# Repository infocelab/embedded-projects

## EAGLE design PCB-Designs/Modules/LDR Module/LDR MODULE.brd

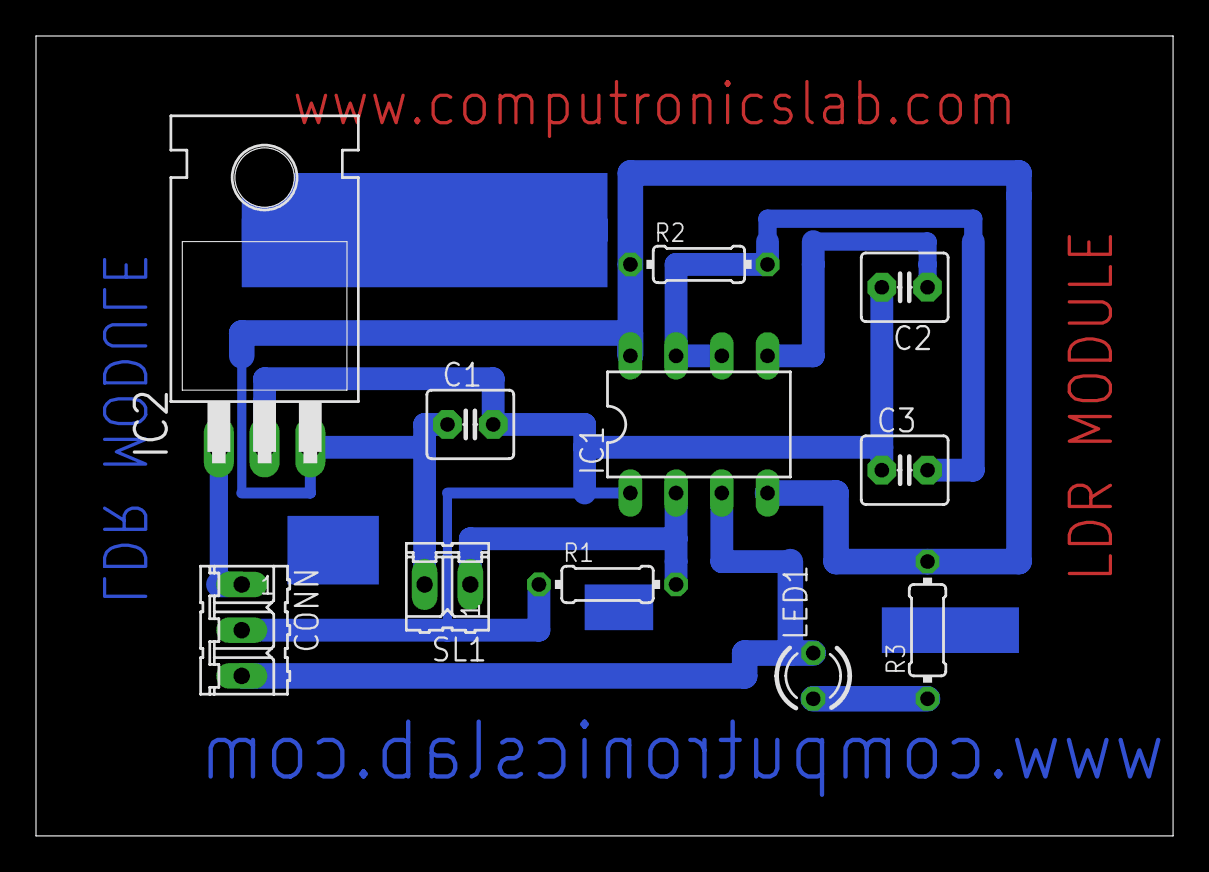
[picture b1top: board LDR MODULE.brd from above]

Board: 2 copper layers, 63.2 x 44.4 mm, 11 parts (0 on the bottom side), 8 nets.

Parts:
C1: .001uf; C2.5-4
C2: 0.01uf; C2.5-4
C3: 0.001uf; C2.5-4
CONN: 3 PIN; 03P
IC1: NE555; DIL-08
IC2: 7805T; TO220H
LED1: 3MM; LED3MM
R1: 10K; 0204/7
R2: 100K; 0204/7
R3: 330E; 0204/7
SL1: LDR; 02P

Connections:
unnamed: C1.1, IC1.4, IC1.8, IC2.3, R2.1, R3.2, SL1.2
unnamed: C3.2, IC1.6, IC1.7, R2.2
unnamed: C2.1, IC1.5
unnamed: IC1.2, R1.2, SL1.1
unnamed: C1.2, C2.2, C3.1, CONN.2, IC1.1, IC2.2, R1.1
unnamed: CONN.3, IC1.3, LED1.K
unnamed: LED1.A, R3.1
unnamed: CONN.1, IC2.1

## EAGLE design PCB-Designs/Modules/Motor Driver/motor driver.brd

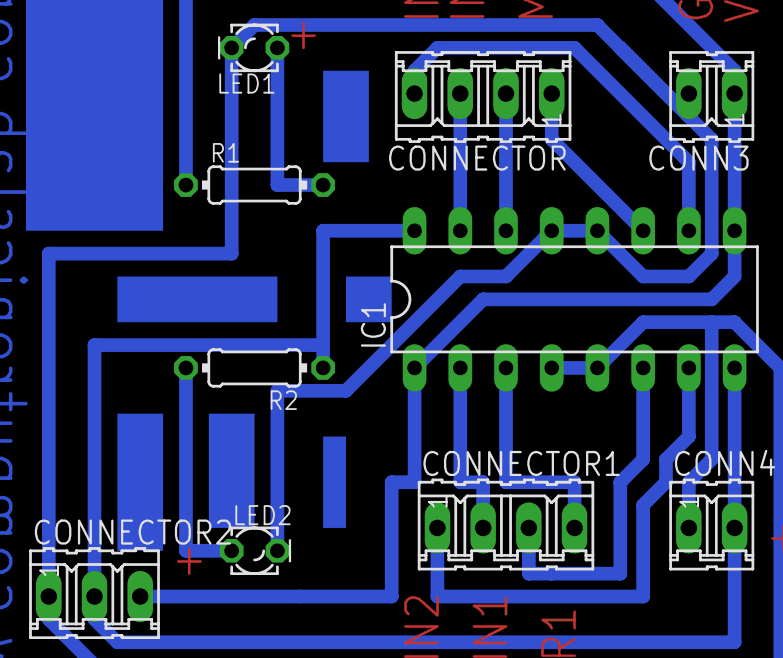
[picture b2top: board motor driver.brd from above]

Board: 2 copper layers, 10 parts (0 on the bottom side), 13 nets.

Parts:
CONN3, CONN4: 2 pin; 02P
CONNECTOR, CONNECTOR1: 4 pin; 04P
CONNECTOR2: 3 pin; 03P
IC1: L293D; DIL16
LED1, LED2: 5mm; LED_LD260
R1, R2: 330E; 0204/7

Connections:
unnamed: LED1.A, R1.2
unnamed: LED2.A, R2.2
unnamed: CONNECTOR1.2, IC1.2
unnamed: CONNECTOR1.4, IC1.3
unnamed: CONNECTOR1.3, IC1.6
unnamed: CONNECTOR1.1, IC1.7
unnamed: CONNECTOR.3, IC1.15
unnamed: CONNECTOR.4, IC1.10
unnamed: CONNECTOR.2, IC1.14
unnamed: CONNECTOR.1, IC1.11
unnamed: CONN3.2, CONN4.1, CONNECTOR2.1, IC1.4, IC1.5, IC1.12, IC1.13, LED1.K, LED2.K
unnamed: CONN3.1, CONNECTOR2.3, IC1.1, IC1.9, R1.1
unnamed: CONN4.2, CONNECTOR2.2, IC1.8, IC1.16, R2.1

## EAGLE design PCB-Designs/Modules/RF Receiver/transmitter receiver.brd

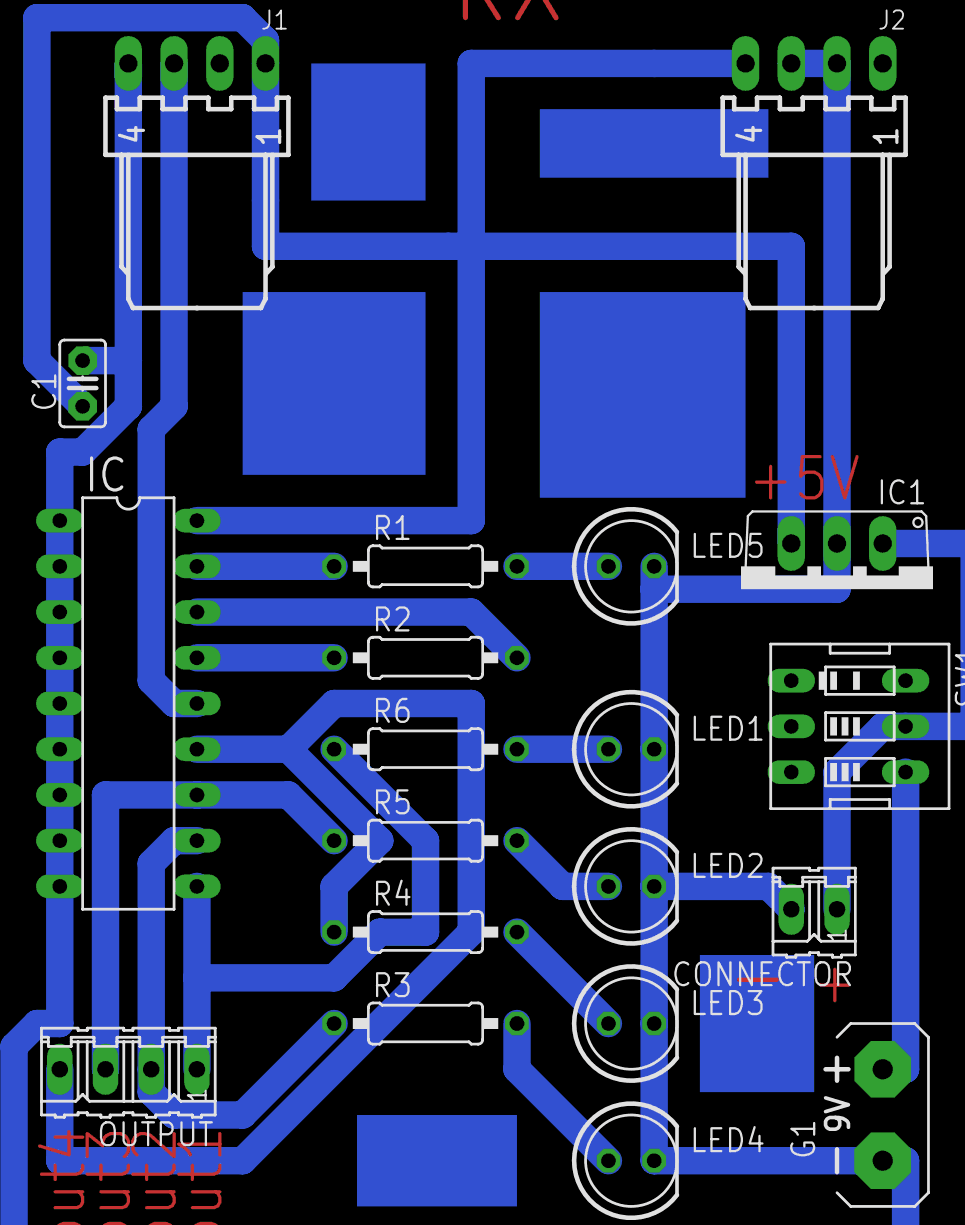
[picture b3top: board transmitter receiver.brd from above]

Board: 2 copper layers, 20 parts (0 on the bottom side), 17 nets.

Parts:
C1: .01uf (103); C2.5-2
CONNECTOR: 2 pin; 02P
G1: AB9V
IC: HT12D; DIL18
IC1: 7805TV; TO220V
J1, J2: female conn; 7395-04
LED1, LED2, LED3, LED4, LED5: 5mm; LED5MM
OUTPUT: 4 pin; 04P
R1, R3, R4, R5, R6: 330E; 0207/10
R2: 47K; 0207/10
SW1: on/off switch; EDG-03

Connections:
FEMALECONN: IC.14, J1.3
unnamed: LED3.A, R4.2
unnamed: LED2.A, R5.2
unnamed: LED4.A, R3.2
unnamed: LED1.A, R6.2
unnamed: IC.15, R2.1
unnamed: IC.17, R1.1
unnamed: LED5.A, R1.2
unnamed: IC.13, OUTPUT.4, R4.1
unnamed: IC.12, OUTPUT.3, R5.1
unnamed: IC.11, OUTPUT.2, R3.1
unnamed: IC.10, OUTPUT.1, R6.1
unnamed: C1.1, IC.18, IC1.3, J1.1, J2.4
unnamed: C1.2, CONNECTOR.2, G1.-, IC.1, IC.2, IC.3, IC.4, IC.5, IC.6, IC.7, IC.8, IC.9, IC1.2, J1.4, J2.2, J2.3, LED1.K, LED2.K, LED3.K, LED4.K, LED5.K
unnamed: G1.+, SW1.4
unnamed: CONNECTOR.1, IC1.1, SW1.5
unnamed: IC.16, R2.2

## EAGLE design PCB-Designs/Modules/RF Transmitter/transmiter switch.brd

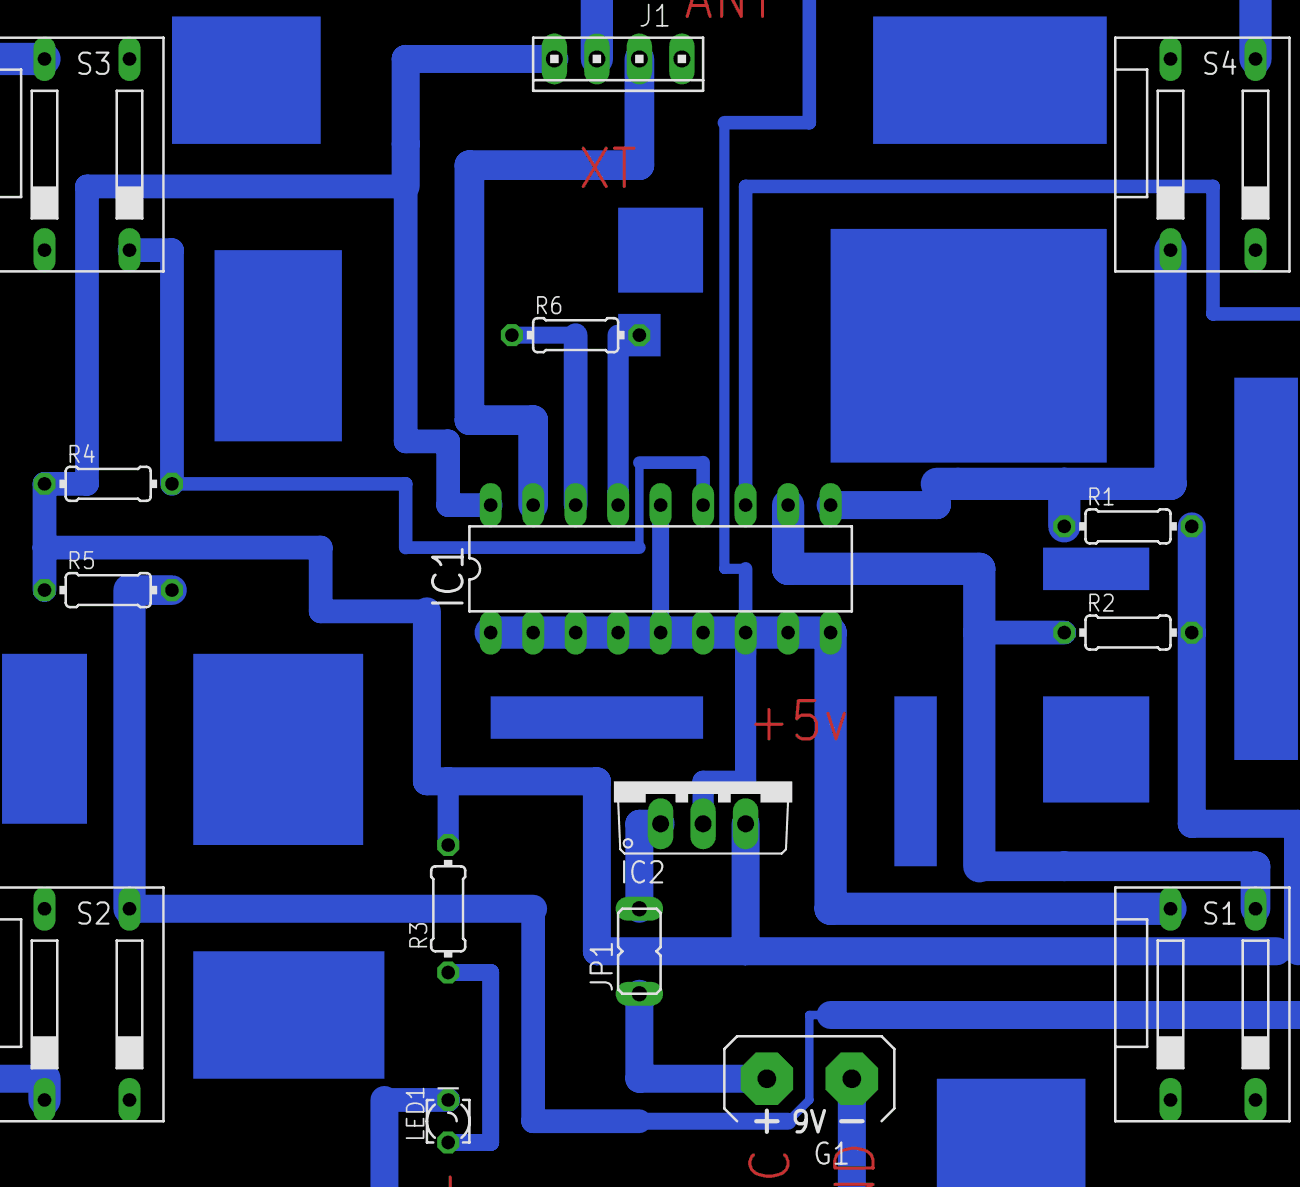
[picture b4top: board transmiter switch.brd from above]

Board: 2 copper layers, 16 parts (0 on the bottom side), 12 nets.

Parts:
G1: AB9V
IC1: HT12E; DIL18
IC2: 7805TV; TO220V
J1: transmitter; 10X04MTA
JP1: jumper; JP1
LED1: 5mm; LED_LD260
R1, R2, R4, R5: 1k; 0204/7
R3: 330E; 0204/7
R6: 1ME; 0204/7
S1: push switch 1; DS-02
S2: push switch2; DS-02
S3: push switch 3; DS-02
S4: push switch 4; DS-02

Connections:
unnamed: LED1.A, R3.1
unnamed: IC1.10, R1.1, S4.1
unnamed: IC1.11, R2.1, S1.3
unnamed: IC1.12, R5.2, S2.3
unnamed: IC1.13, R4.2, S3.2
unnamed: IC1.16, R6.1
unnamed: IC1.15, R6.2
unnamed: IC1.18, IC2.3, J1.1, R1.2, R2.2, R3.2, R4.1, R5.1
unnamed: IC1.17, J1.3
unnamed: G1.-, IC1.1, IC1.2, IC1.3, IC1.4, IC1.5, IC1.6, IC1.7, IC1.8, IC1.9, IC1.14, IC2.2, J1.2, LED1.K, S1.4, S2.1, S3.4, S4.3
unnamed: G1.+, JP1.1
unnamed: IC2.1, JP1.2

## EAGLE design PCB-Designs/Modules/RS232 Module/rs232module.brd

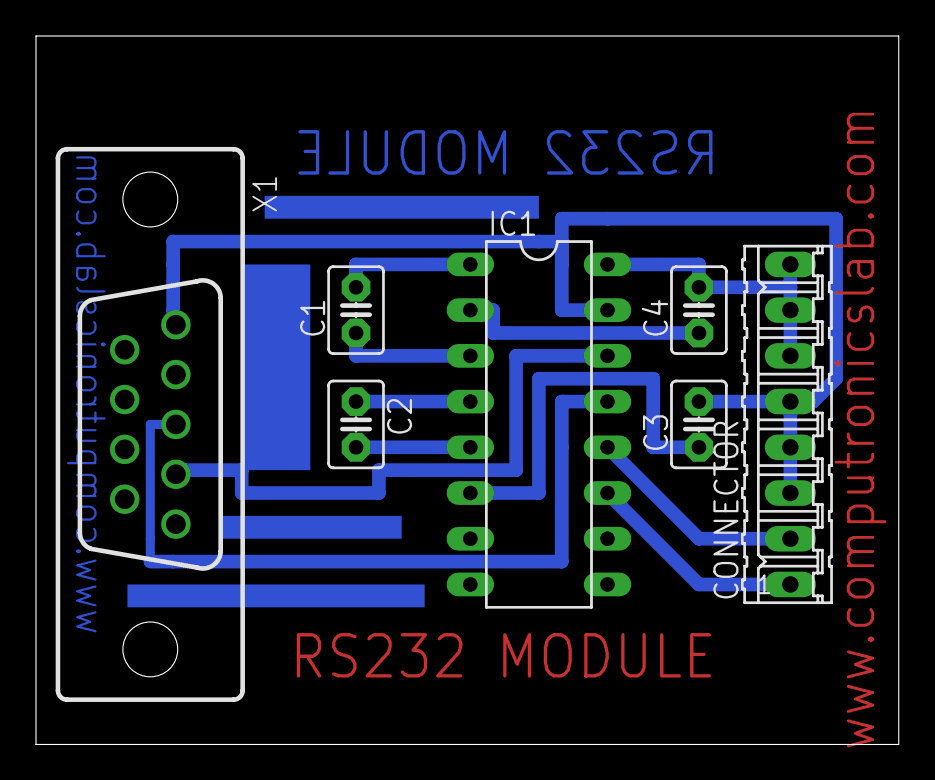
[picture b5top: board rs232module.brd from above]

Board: 2 copper layers, 47.9 x 39.4 mm, 7 parts (0 on the bottom side), 12 nets.

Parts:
C1, C2, C3, C4: 0.1uf; C2.5-3
CONNECTOR: 8 pin; 08P
IC1: MAX232; DIL16
X1: DB 9 FEMALE; H2M09ST

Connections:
unnamed: C1.2, IC1.1
unnamed: C1.1, IC1.3
unnamed: C2.1, IC1.4
unnamed: C2.2, IC1.5
unnamed: C3.1, IC1.6
unnamed: C3.2, CONNECTOR.3, CONNECTOR.4, CONNECTOR.5, IC1.15, X1.1
unnamed: C4.1, IC1.2
unnamed: C4.2, CONNECTOR.6, CONNECTOR.7, CONNECTOR.8, IC1.16
unnamed: IC1.13, X1.3
unnamed: IC1.14, X1.4
unnamed: CONNECTOR.1, IC1.11
unnamed: CONNECTOR.2, IC1.12

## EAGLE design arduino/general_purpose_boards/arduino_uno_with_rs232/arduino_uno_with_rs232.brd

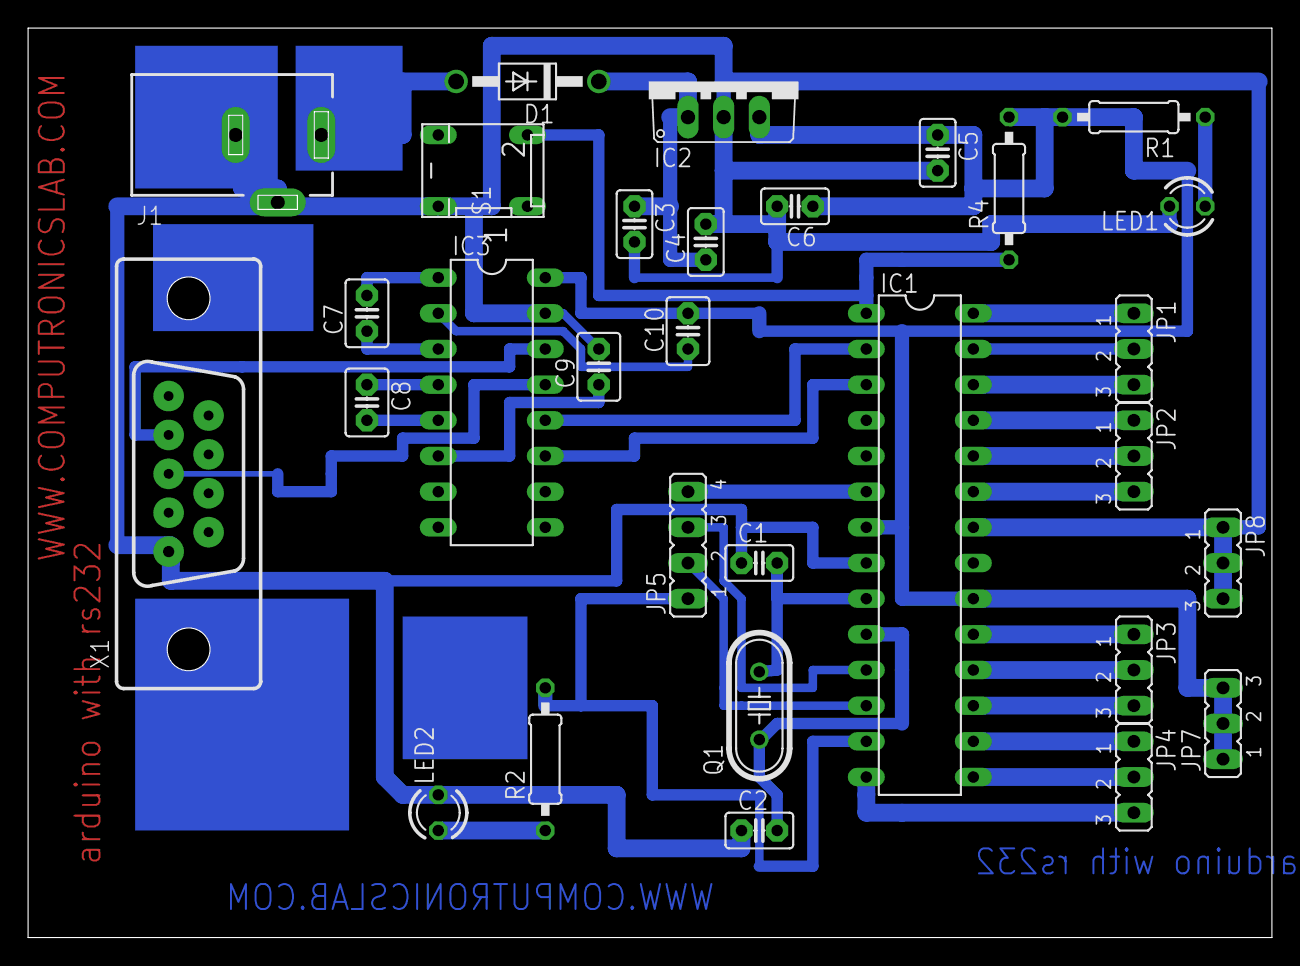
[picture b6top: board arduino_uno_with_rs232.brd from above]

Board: 2 copper layers, 88.6 x 64.8 mm, 30 parts (0 on the bottom side), 35 nets.

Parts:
C1, C2: 22pf; C2.5-2
C3: 100UF; C2.5-2
C4, C5: 0.1uf; C2.5-2
C6: 4.7uf; C2.5-2
C7, C8, C9, C10: 0.1uf; C2.5-3
D1: 1N4007; DO41-10
IC1: ATMEGA328; DIL28-3
IC2: 7805; TO220V
IC3: MAX232; DIL16
J1: DCJ0303
JP1, JP2, JP3, JP4, JP7, JP8: JP2
JP5: JP4
LED1, LED2: LED3MM
Q1: 12MHZ; HC49/S
R1: 220R; 0207/10
R2: 330R; 0207/10
R4: 10K; 0207/10
S1: DP-02
X1: DB 9 FEMALE; H2M09ST

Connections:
unnamed: C1.2, IC1.9, Q1.2
unnamed: C2.2, IC1.10, Q1.1
unnamed: D1.A, J1.1
unnamed: LED1.A, R1.1
unnamed: C3.1, C4.1, D1.C, IC2.1
unnamed: IC1.28, JP1.1
unnamed: IC1.27, JP1.2
unnamed: IC1.26, JP1.3
unnamed: IC1.25, JP2.1
unnamed: IC1.24, JP2.2
unnamed: IC1.23, JP2.3
unnamed: IC1.6, JP5.4
unnamed: IC1.12, JP5.2
unnamed: IC1.11, JP5.3
unnamed: IC1.13, JP5.1, R2.2
unnamed: IC1.14, JP4.3
unnamed: IC1.15, JP4.2
unnamed: IC1.16, JP4.1
unnamed: IC1.17, JP3.3
unnamed: IC1.18, JP3.2
unnamed: IC1.19, JP3.1
unnamed: C7.2, IC3.1
unnamed: C7.1, IC3.3
unnamed: C8.1, IC3.4
unnamed: IC1.1, R4.1, S1.2
unnamed: LED2.A, R2.1
unnamed: C8.2, IC3.5
unnamed: C9.1, IC3.6
unnamed: C1.1, C2.1, C3.2, C4.2, C5.2, C6.2, C9.2, IC1.8, IC1.22, IC2.2, IC3.15, J1.2, J1.3, JP8.1, JP8.2, JP8.3, LED1.K, LED2.K, S1.4, X1.1
unnamed: C10.1, IC3.2
unnamed: C5.1, C6.1, C10.2, IC1.7, IC1.20, IC2.3, IC3.16, JP7.1, JP7.2, JP7.3, R1.2, R4.2
unnamed: IC3.13, X1.3
unnamed: IC3.14, X1.4
unnamed: IC1.3, IC3.11
unnamed: IC1.2, IC3.12

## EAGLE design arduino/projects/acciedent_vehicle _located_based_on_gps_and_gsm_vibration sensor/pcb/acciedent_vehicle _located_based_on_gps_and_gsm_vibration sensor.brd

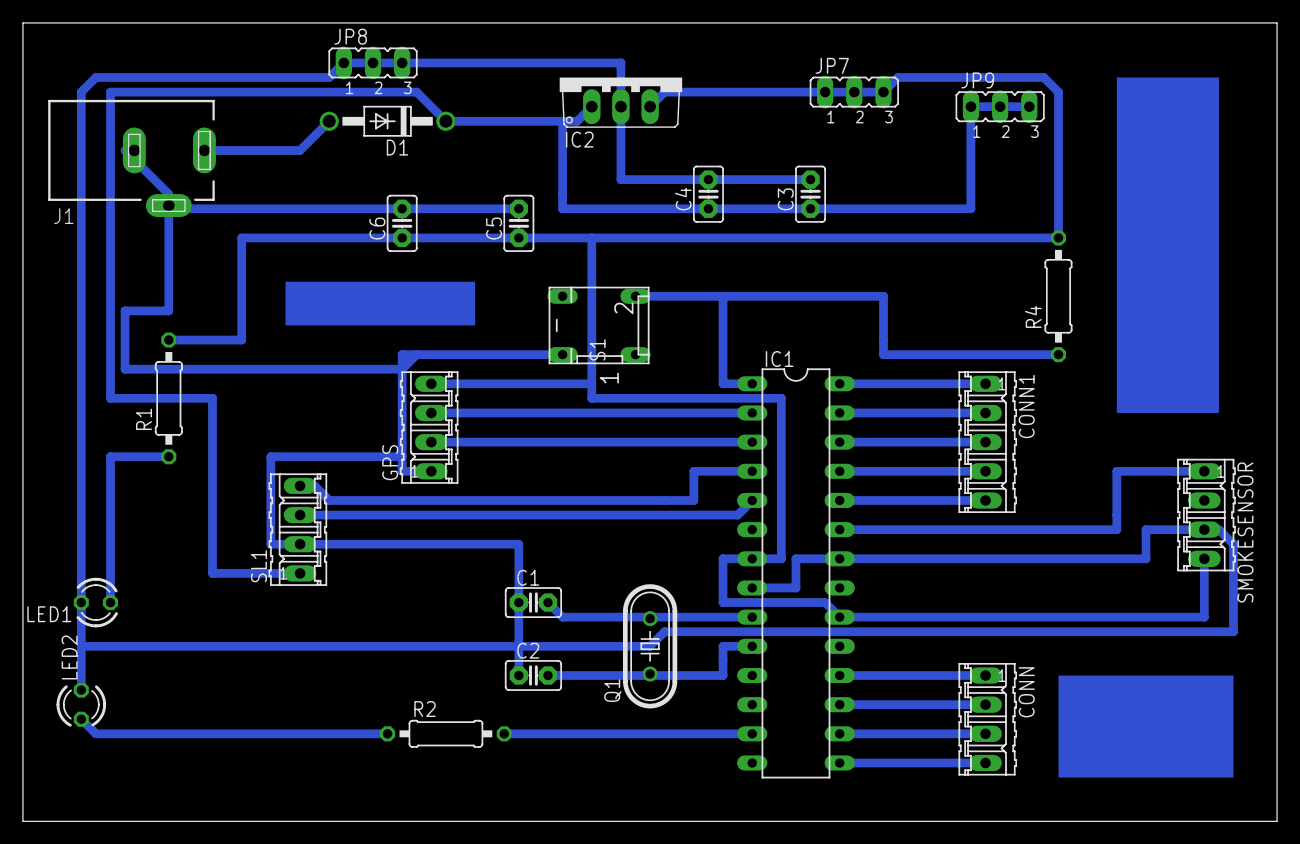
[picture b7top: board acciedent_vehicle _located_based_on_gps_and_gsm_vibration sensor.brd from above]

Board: 2 copper layers, 109.2 x 69.5 mm, 25 parts (0 on the bottom side), 24 nets.

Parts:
C1, C2: 22pf; C2.5-2
C3: 100UF; C2.5-2
C4, C5: 0.1uf; C2.5-2
C6: 4.7uf; C2.5-2
CONN: 04P
CONN1: 05P
D1: 1N4007; DO41-10
GPS: 04P
IC1: ATMEGA328; DIL28-3
IC2: 7805; TO220V
J1: DCJ0303
JP7, JP8, JP9: JP2
LED1, LED2: LED3MM
Q1: 16MHZ; HC49/S
R1: 220R; 0207/10
R2: 330R; 0207/10
R4: 10K; 0207/10
S1: DP-02
SL1: GSM; 04P
SMOKESENSOR: 04P

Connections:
unnamed: C1.2, IC1.9, Q1.2
unnamed: C2.2, IC1.10, Q1.1
unnamed: D1.A, J1.1
unnamed: C5.1, C6.1, GPS.4, IC1.7, IC1.20, IC2.3, JP7.1, JP7.2, JP7.3, R1.2, R4.2, SMOKESENSOR.4
unnamed: C1.1, C2.1, C3.2, C4.2, C5.2, C6.2, GPS.1, IC1.8, IC1.22, IC2.2, J1.2, J1.3, JP8.1, JP8.2, JP8.3, LED1.K, LED2.K, S1.4, SL1.2, SMOKESENSOR.3
unnamed: LED1.A, R1.1
unnamed: C3.1, C4.1, D1.C, IC2.1, JP9.1, JP9.2, JP9.3, SL1.1
unnamed: CONN1.1, IC1.28
unnamed: CONN1.2, IC1.27
unnamed: CONN1.3, IC1.26
unnamed: CONN.1, IC1.18
unnamed: CONN.2, IC1.17
unnamed: IC1.23, SMOKESENSOR.1
unnamed: IC1.5, SL1.3
unnamed: GPS.3, IC1.2
unnamed: GPS.2, IC1.3
unnamed: IC1.4, SL1.4
unnamed: CONN.3, IC1.16
unnamed: CONN.4, IC1.15
unnamed: CONN1.4, IC1.25
unnamed: IC1.13, R2.2
unnamed: CONN1.5, IC1.24
unnamed: IC1.1, R4.1, S1.2
unnamed: LED2.A, R2.1

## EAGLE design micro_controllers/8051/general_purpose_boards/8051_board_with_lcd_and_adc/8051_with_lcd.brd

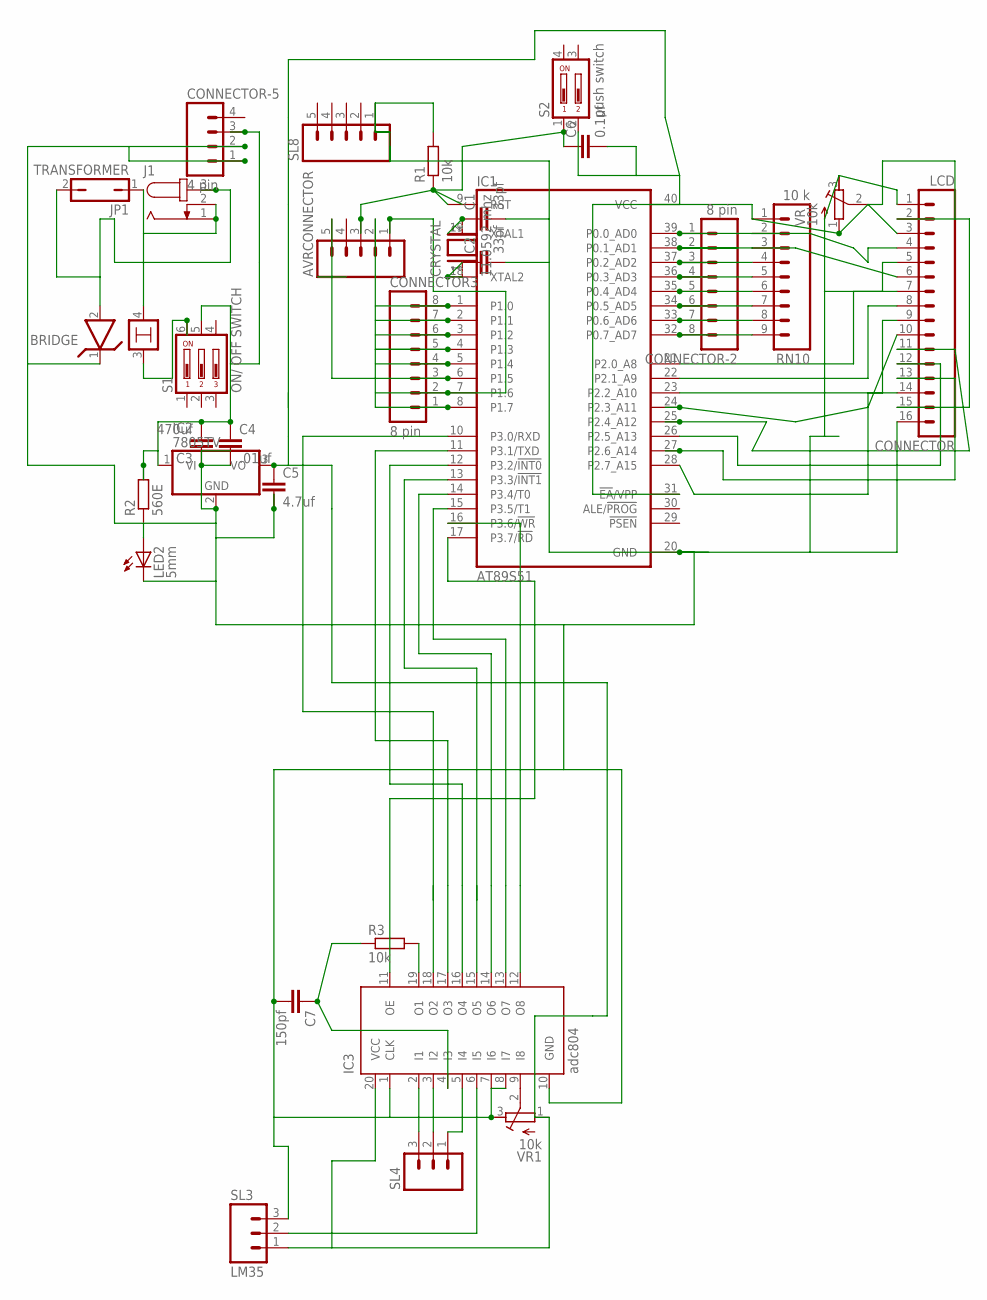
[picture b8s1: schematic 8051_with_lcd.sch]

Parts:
AVRCONNECTOR: M05; 05P
BRIDGE: LM399H; TO39/4
C1, C2: 33pf; C025-024X044
C3: 470uf; C5B7.2
C4: .01uf; C2.5-3
C5: 4.7uf; C2.5-3
C6: 0.1uf; C2.5-6
C7: 150pf; C2.5-3
CONNECTOR: LCD; 16P
CONNECTOR3: 8 pin; 08P
CONNECTOR-2: 8 pin; 08P
CONNECTOR-5: 4 pin; 04P
CRYSTAL: 11.0592 mhz; QS
IC1: AT89S51; DIL40
IC2: 7805TV; TO220V
IC3: adc804; DIL20
J1: JACK-PLUG0; SPC4077
JP1: TRANSFORMER; JP1
LED2: 5mm; LED5MM
R1, R3: 10k; 0204/7
R2: 560E; 0204/7
RN10: 10 k; 09P
S1: ON/ OFF SWITCH; DA-03
S2: push switch; DP-02
SL3: LM35; 03P
SL4: M03; 03P
SL8: M05; 05P
VR, VR1: 10k; RTRIM64P

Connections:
unnamed: C2.1, CRYSTAL.1, IC1.18 (XTAL2)
unnamed: C1.1, CRYSTAL.2, IC1.19 (XTAL1)
unnamed: IC1.10 (P3.0/RXD), IC3.18 (O2)
unnamed: C3.2, C4.1, CONNECTOR-5.3, IC2.1 (VI), R2.2, S1.5
unnamed: BRIDGE.2, J1.3, JP1.2
unnamed: BRIDGE.1, C1.2, C2.2, C3.1, C4.2, C5.2, C7.2, CONNECTOR.1, CONNECTOR.5, CONNECTOR.16, CONNECTOR-5.1, CONNECTOR-5.2, IC1.20 (GND), IC2.2 (GND), IC3.1 (CLK), IC3.7 (I6), IC3.8 (I7), IC3.10 (GND), LED2.K (C), R1.2, SL3.3, SL8.1, VR.3 (A), VR1.3 (A)
unnamed: IC1.11 (P3.1/TXD), IC3.17 (O3)
unnamed: IC1.12 (P3.2/!INT0), IC3.16 (O4)
unnamed: IC1.13 (P3.3/!INT1), IC3.15 (O5)
unnamed: IC1.14 (P3.4/T0), IC3.14 (O6)
unnamed: IC1.15 (P3.5/T1), IC3.13 (O7)
unnamed: IC1.16 (P3.6/!WR), IC3.12 (O8)
unnamed: IC1.17 (P3.7/!RD), IC3.11 (OE)
unnamed: AVRCONNECTOR.3, C6.1, IC1.9 (RST), R1.1, S2.1
unnamed: AVRCONNECTOR.1, CONNECTOR3.2, IC1.7 (P1.6)
unnamed: BRIDGE.4, J1.1, J1.2, JP1.1
unnamed: CONNECTOR3.4, IC1.5 (P1.4)
unnamed: CONNECTOR3.5, IC1.4 (P1.3)
unnamed: CONNECTOR3.6, IC1.3 (P1.2)
unnamed: CONNECTOR3.7, IC1.2 (P1.1)
unnamed: CONNECTOR3.8, IC1.1 (P1.0)
unnamed: IC3.19 (O1), R3.2
unnamed: C7.1, IC3.4 (I3), R3.1
unnamed: CONNECTOR-2.3, IC1.37 (P0.2_AD2), RN10.4
unnamed: CONNECTOR-2.4, IC1.36 (P0.3_AD3), RN10.5
unnamed: CONNECTOR-2.5, IC1.35 (P0.4_AD4), RN10.6
unnamed: CONNECTOR-2.6, IC1.34 (P0.5_AD5), RN10.7
unnamed: CONNECTOR-2.7, IC1.33 (P0.6_AD6), RN10.8
unnamed: CONNECTOR-2.8, IC1.32 (P0.7_AD7), RN10.9
unnamed: CONNECTOR.7, IC1.21 (P2.0_A8)
unnamed: CONNECTOR.8, IC1.22 (P2.1_A9)
unnamed: CONNECTOR.9, IC1.23 (P2.2_A10)
unnamed: IC3.6 (I5), SL3.2
unnamed: IC3.2 (I1), SL4.3
unnamed: CONNECTOR.12, IC1.26 (P2.5_A13)
unnamed: IC3.3 (I2), SL4.2
unnamed: IC3.5 (I4), SL4.1
unnamed: CONNECTOR.3, VR.2 (S)
unnamed: IC3.9 (I8), VR1.2 (S)
unnamed: AVRCONNECTOR.5, CONNECTOR3.3, IC1.6 (P1.5)
unnamed: LED2.A, R2.1
unnamed: AVRCONNECTOR.2, CONNECTOR3.1, IC1.8 (P1.7)
unnamed: BRIDGE.3, S1.6
unnamed: CONNECTOR.6, CONNECTOR-2.2, IC1.38 (P0.1_AD1), RN10.3
unnamed: C5.1, C6.2, CONNECTOR.2, CONNECTOR.15, IC1.31 (!EA!/VPP), IC1.40 (VCC), IC2.3 (VO), IC3.20 (VCC), RN10.1, S2.2, SL3.1, VR.1 (E), VR1.1 (E)
unnamed: CONNECTOR.10, IC1.24 (P2.3_A11)
unnamed: CONNECTOR.11, IC1.25 (P2.4_A12)
unnamed: CONNECTOR.13, IC1.27 (P2.6_A14)
unnamed: CONNECTOR.14, IC1.28 (P2.7_A15)
unnamed: CONNECTOR.4, CONNECTOR-2.1, IC1.39 (P0.0_AD0), RN10.2

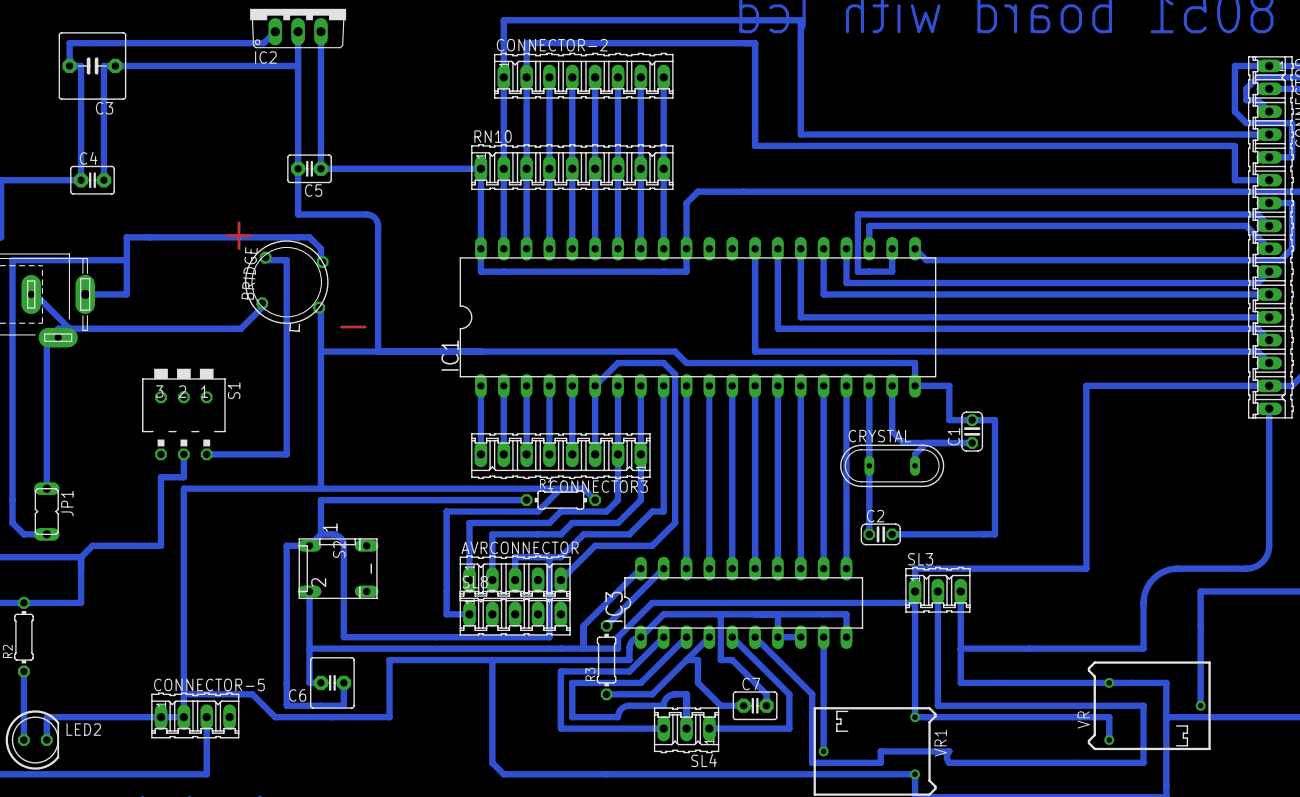
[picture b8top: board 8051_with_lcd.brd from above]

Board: 2 copper layers, 31 parts (0 on the bottom side), 50 nets.
